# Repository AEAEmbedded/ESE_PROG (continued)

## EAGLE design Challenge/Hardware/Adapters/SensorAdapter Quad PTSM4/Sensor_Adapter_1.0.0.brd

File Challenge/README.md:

# Challenge

This folder contains resources for the Prog6 Challenge project.

## Repositories

- **[PiTest](https://github.com/jakorten/PiTest)** - Raspberry Pi 4 to SensorHub (SAMD21) I2C communication test
  - Python I2C test script for Pi
  - C++ Arduino sketch for SAMD21
  - Pinout documentation

## Contents

- **HAN_Challenge_Prog_6_2025.pdf** - Challenge assignment document (2025 edition; to be updated for 2026-2027)
- **Hardware/** - Hardware design files and schematics

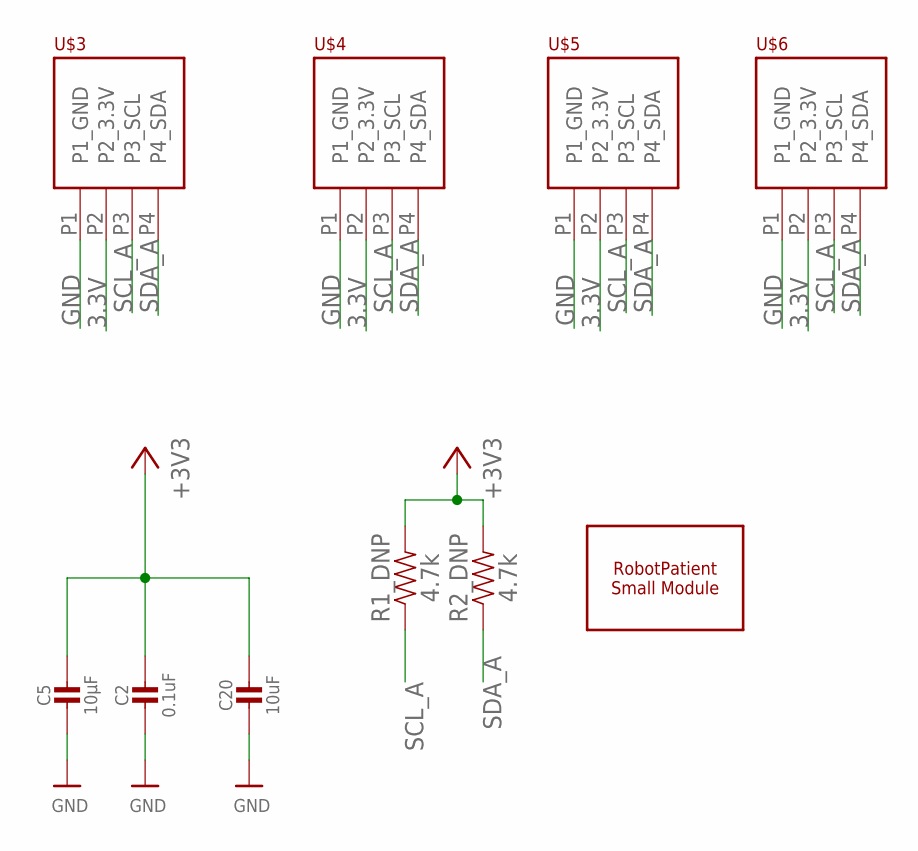
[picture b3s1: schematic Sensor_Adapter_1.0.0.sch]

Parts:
C2: 0.1uF; 0603
C5: 10µF; 0805
C20: 10uF; 0805
R1_DNP, R2_DNP: 4.7k; 0603
U$1: ROBOTPATIENT_SMALL_MODULEBOARD; RP_SMALL_SENSOR_OUTLINE
U$3, U$4, U$5, U$6: PHOENIX_PTSM_M4_THANGLE; PTSM_M4_TH

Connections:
3.3V: C2.1, C5.1, C20.1, R1_DNP.2, R2_DNP.2, U$3.P2 (P2_3.3V), U$4.P2 (P2_3.3V), U$5.P2 (P2_3.3V), U$6.P2 (P2_3.3V)
GND: C2.2, C5.2, C20.2, U$3.P1 (P1_GND), U$4.P1 (P1_GND), U$5.P1 (P1_GND), U$6.P1 (P1_GND)
SCL_A: R1_DNP.1, U$3.P3 (P3_SCL), U$4.P3 (P3_SCL), U$5.P3 (P3_SCL), U$6.P3 (P3_SCL)
SDA_A: R2_DNP.1, U$3.P4 (P4_SDA), U$4.P4 (P4_SDA), U$5.P4 (P4_SDA), U$6.P4 (P4_SDA)

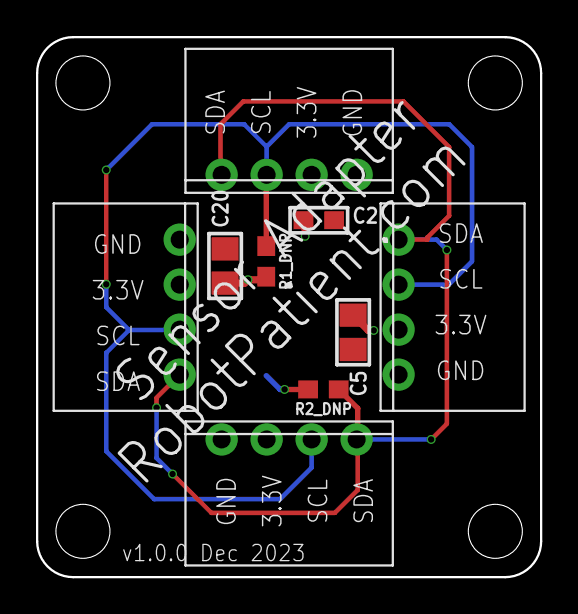
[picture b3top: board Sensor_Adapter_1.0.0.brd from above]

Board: 2 copper layers, 28.0 x 30.0 mm, 10 parts (0 on the bottom side), 4 nets.

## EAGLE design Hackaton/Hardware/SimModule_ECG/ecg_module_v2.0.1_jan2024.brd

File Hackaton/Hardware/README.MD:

# Patient Monitoring System on Raspberry Pi 3

This project involves creating a patient monitoring system using Raspberry Pi 3, which interfaces with various medical sensor modules (ECG, SpO2, NIBP, Temperature) via I2C and other communication protocols. The system features a simple and intuitive user interface for real-time monitoring.

### Table of Contents

- Overview
- Hardware Requirements
- Software Requirements
- Setup Guide
- System Architecture
- Usage
- Future Enhancements
- Overview

## The Patient Monitoring System collects and displays vital signs such as:

- ECG (Electrocardiogram)
- SpO2 (Oxygen Saturation)
- NIBP (Non-Invasive Blood Pressure)
- Temperature

The system is modular and allows integration of additional sensors through standardized adapters and communication protocols.

## Hardware Requirements

Raspberry Pi 3 (or higher) with GPIO-enabled interface

### Sensor Modules:
- ECG: ecg_leaddetection_module
- SpO2: spo2_module
- Temperature: temp_module
- NIBP: Pressure_Module

### Adapters:
- SensorAdapter Quad PTSM4
- SimModule Adapter

### Connections:
- I2C: SDA (GPIO2) and SCL (GPIO3)
- UART or SPI (if required by modules)

Refer to the provided .brd and .sch files for hardware schematics.

  * [hardware](./)
    * [Adapters](./Adapters) - PCB schematics and board files for adapters
    * [SimModule_ECG](./SimModule_ECG) - ECG sensor module files
    * [SimModule_NIBP](./SimModule_NIBP) - Blood pressure (NIBP) module files
    * [SimModule_SpO2](./SimModule_SpO2) - SpO2 (Oxygen saturation) module files
    * [SimModule_Temperature](./SimModule_Temperature) - Temperature module files
  * [README.md](README.md) - Documentation file (this file)

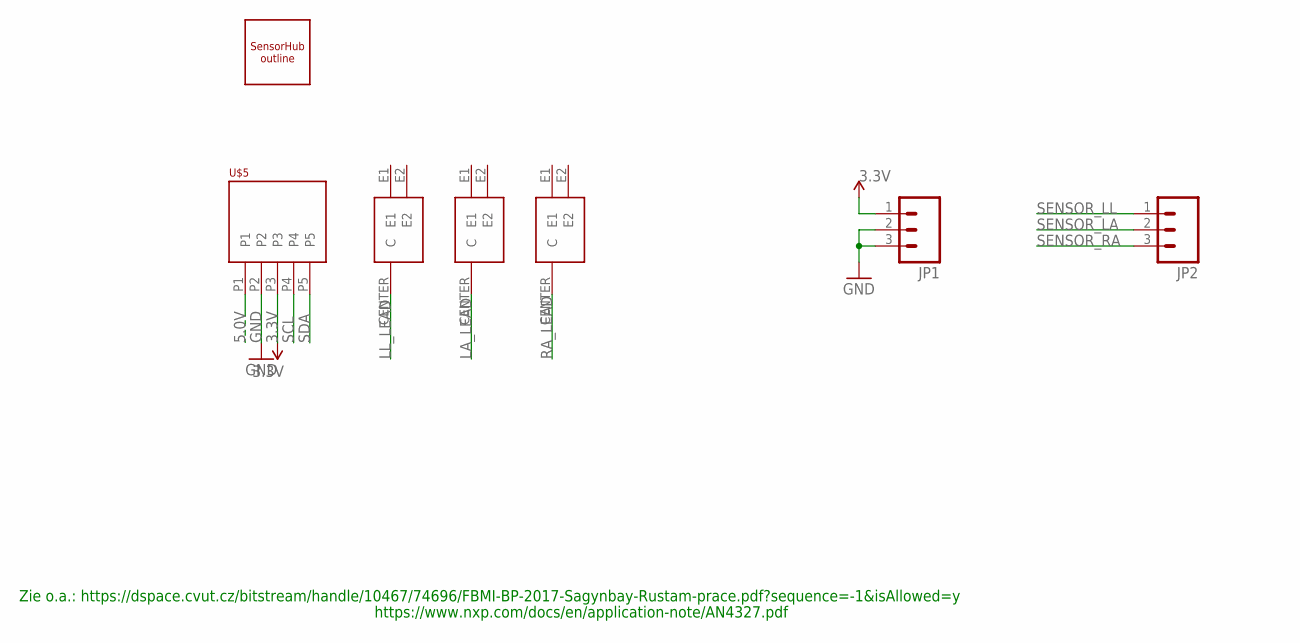
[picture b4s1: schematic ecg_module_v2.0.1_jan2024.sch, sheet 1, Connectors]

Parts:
JP1, JP2: M03PTH; 1X03
U$1, U$3, U$4: DIN_ECG_EEG; EEG_ECG_DIN
U$5: PHOENIX_PTSM_M5_TH_I2C++; PTSM_M5_THRHOLE
U$12: SENSORHUB_PROFILEUSB_LEFT; SENSORHUB_OUTLINE_USB_NOTCH_LEFT

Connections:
3.3V: JP1.1, U$5.P3; also elsewhere on the board
5.0V: U$5.P1; also elsewhere on the board
GND: JP1.2, JP1.3, U$5.P2; also elsewhere on the board
LA_LEAD: U$3.CENTER (C); also elsewhere on the board
LL_LEAD: U$1.CENTER (C); also elsewhere on the board
RA_LEAD: U$4.CENTER (C); also elsewhere on the board
SCL: U$5.P4; also elsewhere on the board
SDA: U$5.P5; also elsewhere on the board
SENSOR_LA: JP2.2; also elsewhere on the board
SENSOR_LL: JP2.1; also elsewhere on the board
SENSOR_RA: JP2.3; also elsewhere on the board

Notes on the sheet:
Zie o.a.: https://dspace.cvut.cz/bitstream/handle/10467/74696/FBMI-BP-2017-Sagynbay-Rustam-prace.pdf?sequence=-1&isAllowed=y
https://www.nxp.com/docs/en/application-note/AN4327.pdf

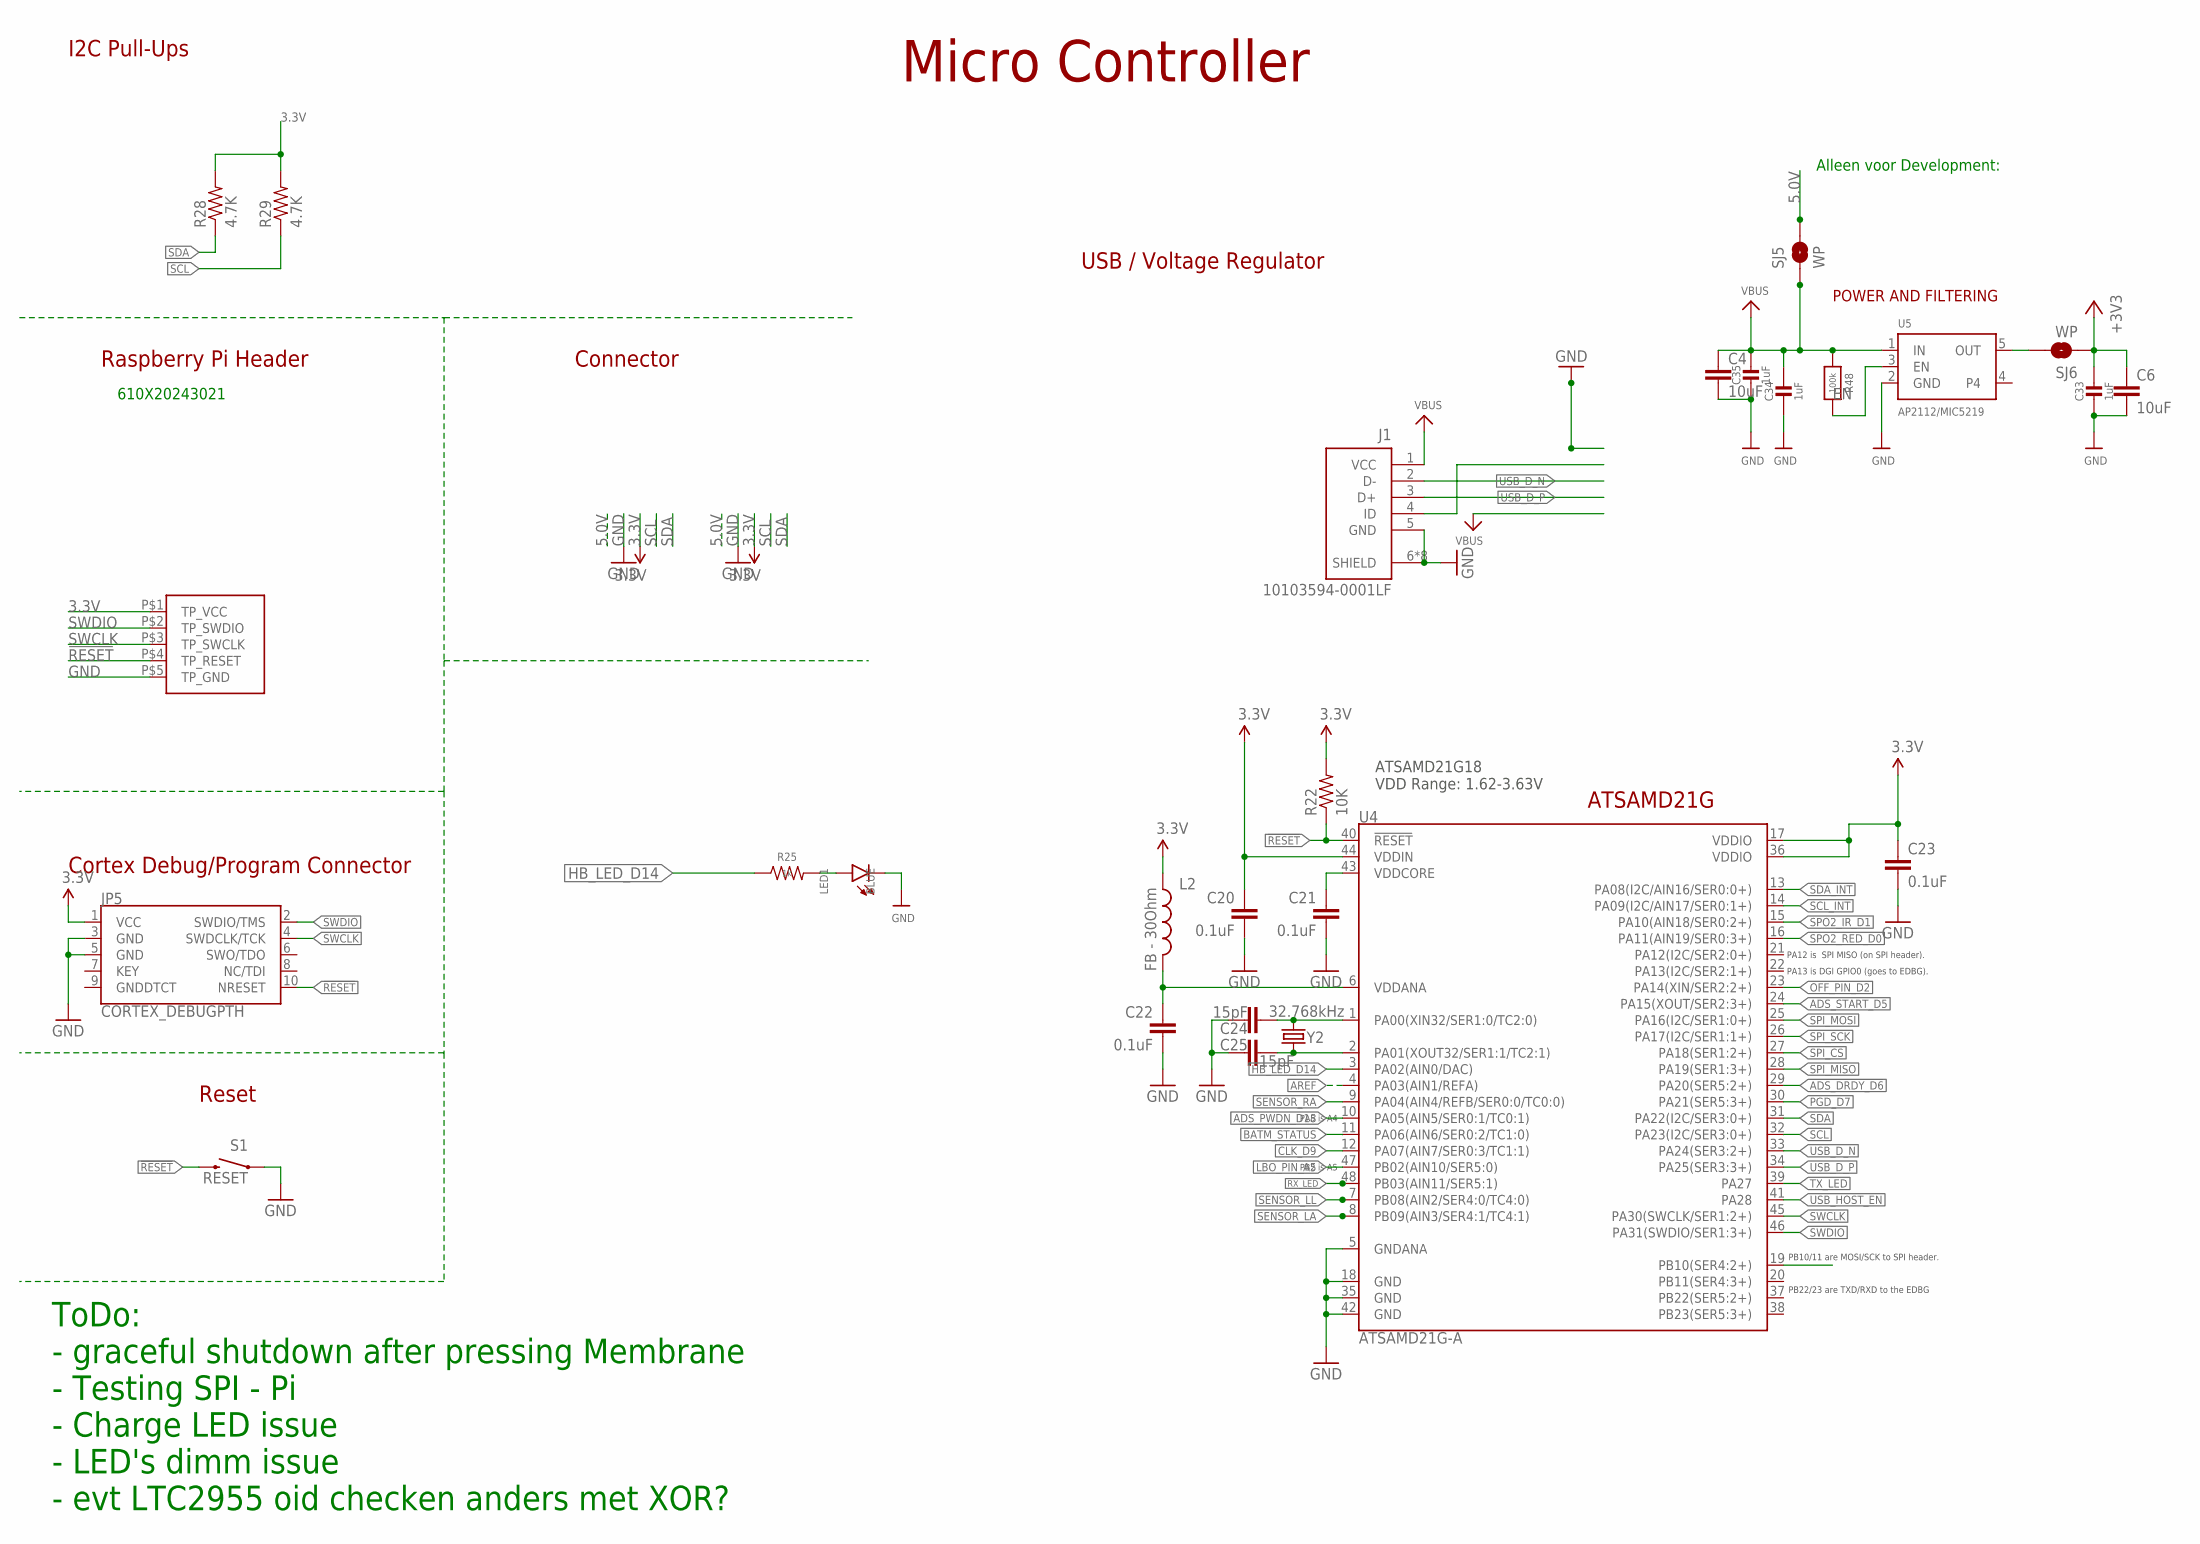
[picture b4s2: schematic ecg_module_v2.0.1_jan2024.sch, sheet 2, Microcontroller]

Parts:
C4, C6: 10uF; 0603
C20, C22, C23: 0.1uF; 0402-CAP
C21: 0.1uF; 0603
C24, C25: 15pF; 0402-CAP
C33, C34, C35: 1uF; 0603-NO
J1: 10103594-0001LF; AMPHENOL_10103594-0001LF
JP5: CORTEX_DEBUGPTH; 2X5-PTH-1.27MM
L2: FB - 30Ohm; 0603
LED1: BLUE; CHIP-LED0603
R22: 10K; 0603-RES
R25: 1k; 0603
R28, R29: 4.7K; 0603-RES
R48: 100k; 0603-NO@1
S1: RESET; TACTILE_SWITCH_SMD_4.6X2.8MM
SJ5, SJ6: WP; SMT-JUMPER_2_NO_NO-SILK
U4: ATSAMD21G-A; TQFP-48
U5: AP2112/MIC5219; SOT23-5
U$9: HUB_TESTPINSHUBS; TEST_PINS
Y2: 32.768kHz; CRYSTAL-SMD-3.2X1.5MM

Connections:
3.3V: C6.1, C20.1, C23.1, C33.1, JP5.1 (VCC), L2.1, R22.2, R28.2, R29.2, SJ6.1, U4.17 (VDDIO), U4.36 (VDDIO), U4.44 (VDDIN), U$9.P$1 (TP_VCC); also elsewhere on the board
5.0V: SJ5.2; also elsewhere on the board
!ADS_DRDY_D6: U4.29 (PA20(SER5:2+)); also elsewhere on the board
!RESET: JP5.10 (NRESET), R22.1, S1.3 (2), S1.4 (2), U4.40 (!RESET!), U$9.P$4 (TP_RESET)
ADS_PWDN_D18: U4.10 (PA05(AIN5/SER0:1/TC0:1)); also elsewhere on the board
ADS_START_D5: U4.24 (PA15(XOUT/SER2:3+)); also elsewhere on the board
AREF: U4.4 (PA03(AIN1/REFA))
BATM_STATUS: U4.11 (PA06(AIN6/SER0:2/TC1:0))
CLK_D9: U4.12 (PA07(AIN7/SER0:3/TC1:1)); also elsewhere on the board
EN: R48.2, U5.3 (EN)
GND: C4.2, C6.2, C20.2, C21.2, C22.2, C23.2, C24.1, C25.2, C33.2, C34.2, C35.2, J1.5 (GND), J1.6 (SHIELD), J1.7 (SHIELD), J1.8 (SHIELD), J1.9 (SHIELD), J1.10 (SHIELD), J1.11 (SHIELD), J1.S1 (SHIELD), J1.S2 (SHIELD), JP5.3 (GND), JP5.5 (GND), LED1.C, S1.1, S1.2 (1), U4.5 (GNDANA), U4.18 (GND), U4.35 (GND), U4.42 (GND), U5.2 (GND), U$9.P$5 (TP_GND); also elsewhere on the board
HB_LED_D14: R25.1, U4.3 (PA02(AIN0/DAC))
LBO_PIN_A5: U4.47 (PB02(AIN10/SER5:0))
unnamed: LED1.A, R25.2
unnamed: C24.2, U4.1 (PA00(XIN32/SER1:0/TC2:0)), Y2.P$2 (2)
unnamed: C25.1, U4.2 (PA01(XOUT32/SER1:1/TC2:1)), Y2.P$1 (1)
OFF_PIN_D2: U4.23 (PA14(XIN/SER2:2+))
OUT: SJ6.2, U5.5 (OUT)
PGD_D7: U4.30 (PA21(SER5:3+))
RX_LED: U4.48 (PB03(AIN11/SER5:1))
SCL: R29.1, U4.32 (PA23(I2C/SER3:0+)); also elsewhere on the board
SCL_INT: U4.14 (PA09(I2C/AIN17/SER0:1+))
SDA: R28.1, U4.31 (PA22(I2C/SER3:0+)); also elsewhere on the board
SDA_INT: U4.13 (PA08(I2C/AIN16/SER0:0+))
SENSOR_LA: U4.8 (PB09(AIN3/SER4:1/TC4:1)); also elsewhere on the board
SENSOR_LL: U4.7 (PB08(AIN2/SER4:0/TC4:0)); also elsewhere on the board
SENSOR_RA: U4.9 (PA04(AIN4/REFB/SER0:0/TC0:0)); also elsewhere on the board
SPI_CS: U4.27 (PA18(SER1:2+)); also elsewhere on the board
SPI_MISO: U4.28 (PA19(SER1:3+)); also elsewhere on the board
SPI_MOSI: U4.25 (PA16(I2C/SER1:0+)); also elsewhere on the board
SPI_SCK: U4.26 (PA17(I2C/SER1:1+)); also elsewhere on the board
SPO2_IR_D1: U4.15 (PA10(AIN18/SER0:2+))
SPO2_RED_D0: U4.16 (PA11(AIN19/SER0:3+))
SWCLK: JP5.4 (SWDCLK/TCK), U4.45 (PA30(SWCLK/SER1:2+)), U$9.P$3 (TP_SWCLK)
SWDIO: JP5.2 (SWDIO/TMS), U4.46 (PA31(SWDIO/SER1:3+)), U$9.P$2 (TP_SWDIO)
TX_LED: U4.39 (PA27)
USB_D_N: J1.2 (D-), U4.33 (PA24(SER3:2+))
USB_D_P: J1.3 (D+), U4.34 (PA25(SER3:3+))
USB_HOST_EN: U4.41 (PA28)
VBUS: C4.1, C34.1, C35.1, J1.1 (VCC), R48.1, SJ5.1, U5.1 (IN)
VDDANA: C22.1, L2.2, U4.6 (VDDANA)
VDDCORE: C21.1, U4.43 (VDDCORE)

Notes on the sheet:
PB22/23 are TXD/RXD to the EDBG
PB10/11 are MOSI/SCK to SPI header.
PA12 is SPI MISO (on SPI header).
PA13 is DGI GPIO0 (goes to EDBG).
PA5 is A4
PB2 is A5
ATSAMD21G
ATSAMD21G18 VDD Range: 1.62-3.63V
Cortex Debug/Program Connector
USB / Voltage Regulator
I2C Pull-Ups
Micro Controller
Raspberry Pi Header
Connector
Reset
ToDo: - graceful shutdown after pressing Membrane - Testing SPI - Pi - Charge LED issue - LED's dimm issue - evt LTC2955 oid checken anders met XOR?
610X20243021
POWER AND FILTERING
Alleen voor Development:

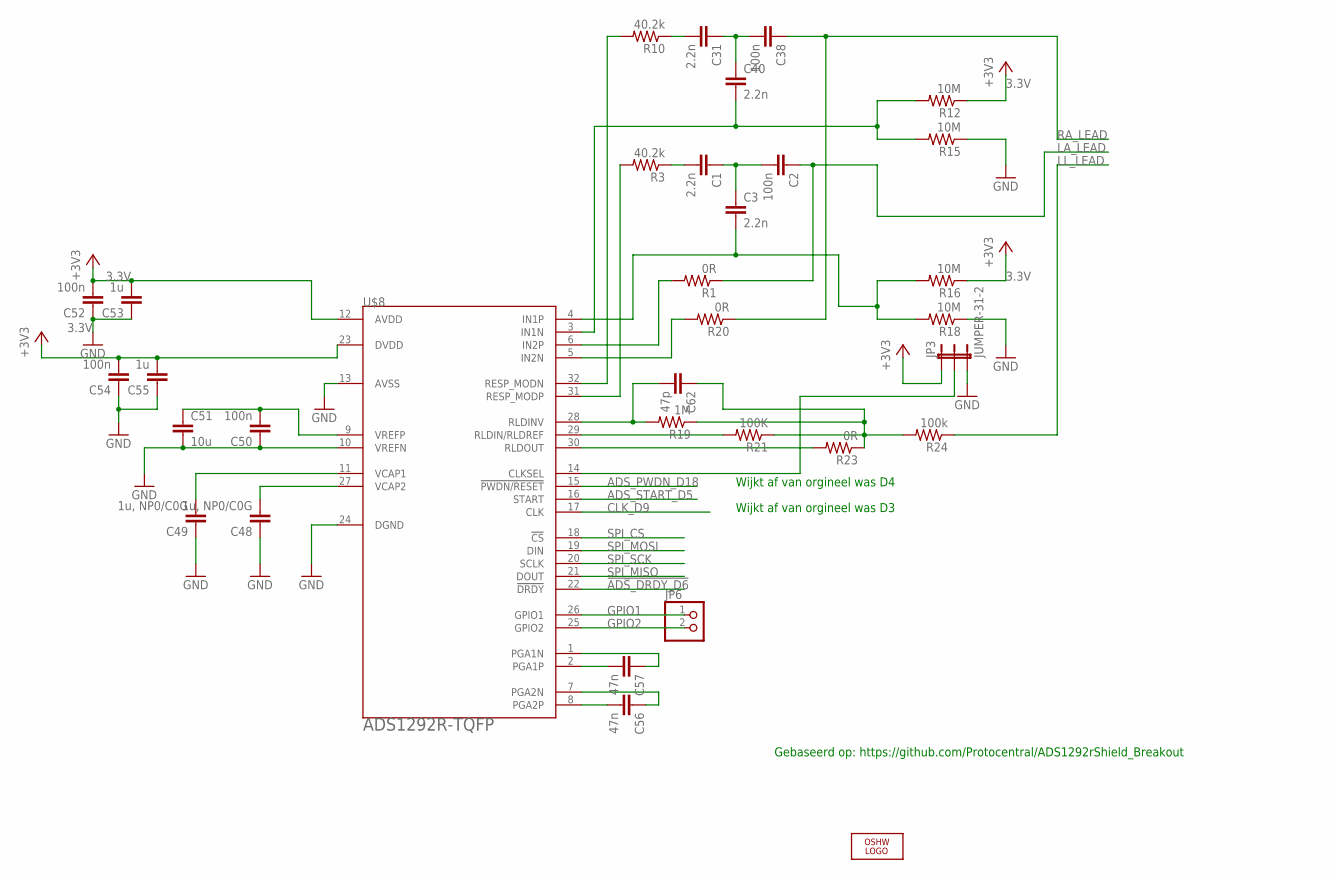
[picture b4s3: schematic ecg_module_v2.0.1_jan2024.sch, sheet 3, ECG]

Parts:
C1, C3, C31, C40: 2.2n; C0402
C2, C38, C50, C52, C54: 100n; C0402
C48, C49: 1u, NP0/C0G; C0402
C51: 10u; C0603
C53, C55: 1u; C0402
C56, C57: 47n; C0402
C62: 47p; C0402
JP3: JUMPER-31-2; SJ_3_PASTE1&2
JP6: PINHD-1X2; 1X02
LOGO1: OSHW_LOGO_FILLX0100-NT; OSHW_FILLX100_NOTEXT
R1, R20, R23: 0R; R0402
R3, R10: 40.2k; R0402
R12, R15, R16, R18: 10M; R0402
R19: 1M; R0402
R21: 100K; R0402
R24: 100k; R0402
U$8: ADS1292R-TQFP; SQFP-S-5X5-32

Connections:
3.3V: C52.2, C53.2, C54.2, C55.2, JP3.1, R12.1, R16.1, U$8.12 (AVDD), U$8.23 (DVDD); also elsewhere on the board
!ADS_DRDY_D6: U$8.22 (!DRDY); also elsewhere on the board
ADS_PWDN_D18: U$8.15 (!PWDN/RESET); also elsewhere on the board
ADS_START_D5: U$8.16 (START); also elsewhere on the board
CLK_D9: U$8.17 (CLK); also elsewhere on the board
GND: C48.1, C49.1, C50.1, C51.2, C52.1, C53.1, C54.1, C55.1, JP3.3, R15.1, R18.1, U$8.10 (VREFN), U$8.13 (AVSS), U$8.24 (DGND); also elsewhere on the board
GPIO1: JP6.1, U$8.26 (GPIO1)
GPIO2: JP6.2, U$8.25 (GPIO2)
LA_LEAD: C2.1, R1.1; also elsewhere on the board
LL_LEAD: R24.1; also elsewhere on the board
unnamed: R3.2, U$8.31 (RESP_MODP)
unnamed: C1.2, R3.1
unnamed: C1.1, C2.2, C3.1
unnamed: R1.2, U$8.6 (IN2P)
unnamed: R20.2, U$8.5 (IN2N)
unnamed: C48.2, U$8.27 (VCAP2)
unnamed: R10.2, U$8.32 (RESP_MODN)
unnamed: C31.2, R10.1
unnamed: C31.1, C38.2, C40.1
unnamed: C40.2, R12.2, R15.2, U$8.3 (IN1N)
unnamed: C3.2, R16.2, R18.2, U$8.4 (IN1P)
unnamed: R21.2, U$8.29 (RLDIN/RLDREF)
unnamed: C62.2, R19.2, U$8.28 (RLDINV)
unnamed: C62.1, R19.1, R21.1, R23.1, R24.2
unnamed: C49.2, U$8.11 (VCAP1)
unnamed: C56.2, U$8.8 (PGA2P)
unnamed: C56.1, U$8.7 (PGA2N)
unnamed: C50.2, C51.1, U$8.9 (VREFP)
unnamed: C57.2, U$8.2 (PGA1P)
unnamed: C57.1, U$8.1 (PGA1N)
unnamed: R23.2, U$8.30 (RLDOUT)
unnamed: JP3.2, U$8.14 (CLKSEL)
RA_LEAD: C38.1, R20.1; also elsewhere on the board
SPI_CS: U$8.18 (!CS); also elsewhere on the board
SPI_MISO: U$8.21 (DOUT); also elsewhere on the board
SPI_MOSI: U$8.19 (DIN); also elsewhere on the board
SPI_SCK: U$8.20 (SCLK); also elsewhere on the board

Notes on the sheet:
Gebaseerd op: https://github.com/Protocentral/ADS1292rShield_Breakout
Wijkt af van orgineel was D3
Wijkt af van orgineel was D4

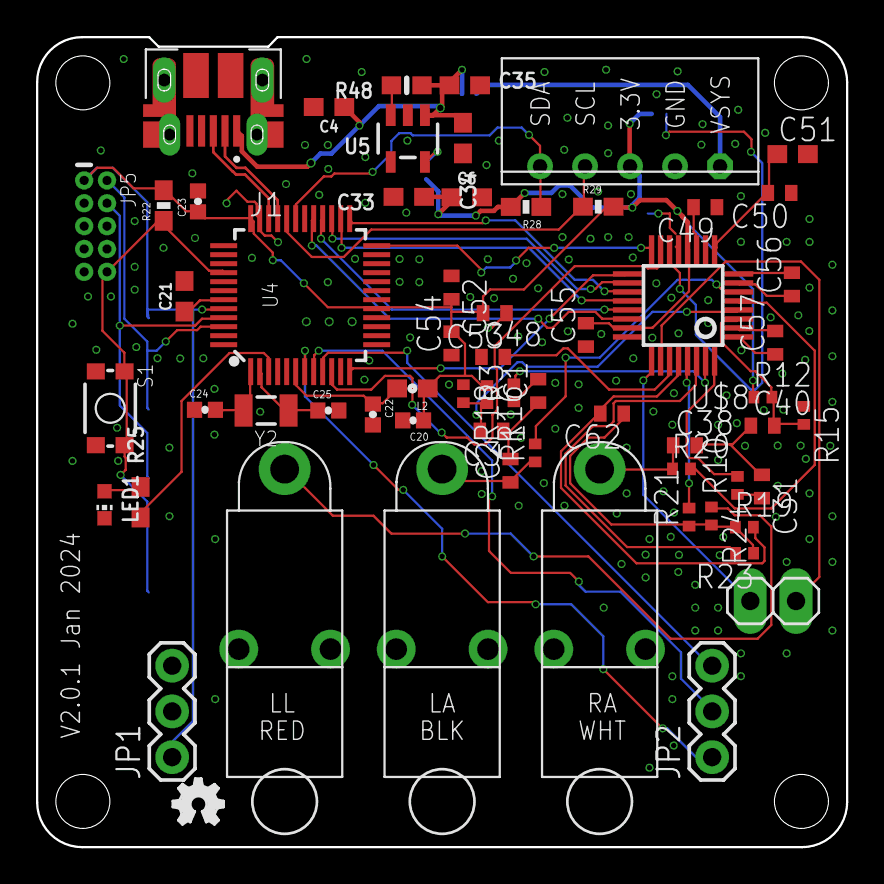
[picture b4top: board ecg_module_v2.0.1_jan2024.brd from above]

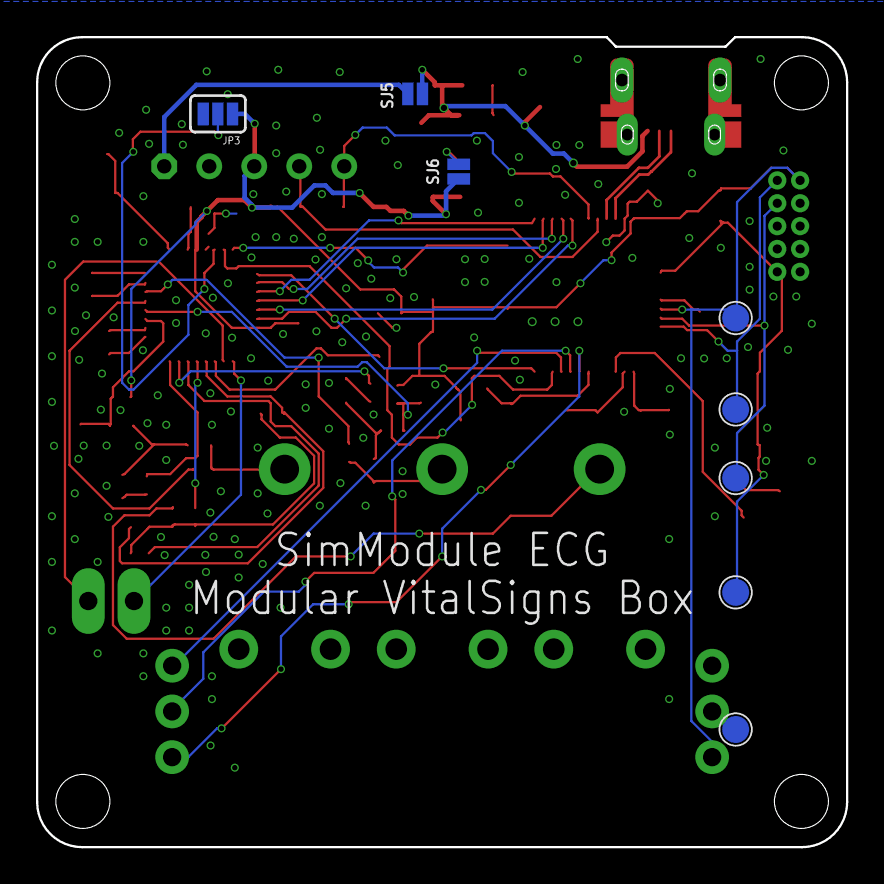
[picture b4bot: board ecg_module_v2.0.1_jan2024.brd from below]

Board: 2 copper layers, 45.0 x 45.0 mm, 67 parts (3 on the bottom side), 57 nets.

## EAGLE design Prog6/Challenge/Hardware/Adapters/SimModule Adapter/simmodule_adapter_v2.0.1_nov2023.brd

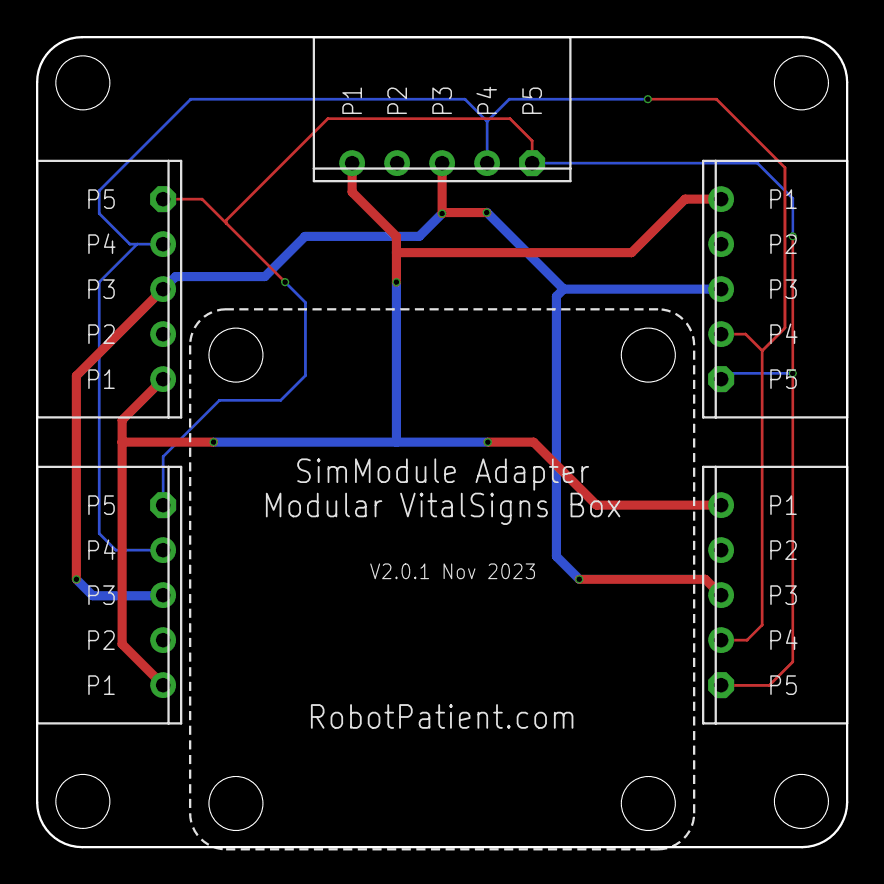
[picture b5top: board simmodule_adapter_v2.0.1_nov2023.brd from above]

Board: 2 copper layers, 45.0 x 45.0 mm, 7 parts (0 on the bottom side), 5 nets.

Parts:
U$1: SENSORHUB_PROFILEBOARD; SENSORHUB_OUTLINE
U$2: ROBOTPATIENT_SMALL_MODULEOUTLINE; ROBOTPATIENT_SMALL
U$3, U$4, U$5, U$6, U$7: PHOENIX_PTSM_M5_NEUTRAL; PTSM_M5_TH_NEUTRAL

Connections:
A: U$3.P1, U$4.P1, U$5.P1, U$6.P1, U$7.P1
B: U$3.P2, U$4.P2, U$5.P2, U$6.P2, U$7.P2
C: U$3.P3, U$4.P3, U$5.P3, U$6.P3, U$7.P3
E: U$3.P5, U$4.P5, U$5.P5, U$6.P5, U$7.P5
GND: U$3.P4, U$4.P4, U$5.P4, U$6.P4, U$7.P4

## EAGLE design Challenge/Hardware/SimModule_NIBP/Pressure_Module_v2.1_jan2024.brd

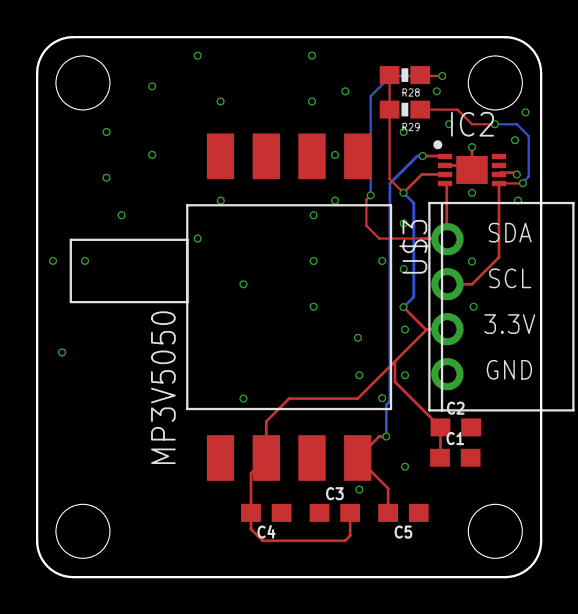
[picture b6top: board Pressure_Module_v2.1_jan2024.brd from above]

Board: 2 copper layers, 28.0 x 30.0 mm, 11 parts (0 on the bottom side), 5 nets.

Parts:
C1: 0.1uF; 0603
C2: 10uF; 0603
C3: 1.0uF; 0603
C4: 10nF; 0603
C5: 470pF; 0603
IC2: MCP3426A0-E_MC; SON50P300X200X100-9N
R28, R29: 4.7K; 0603-RES
U$1: PHOENIX_PTSM_M4_THANGLE; PTSM_M4_TH
U$2: ROBOTPATIENT_SMALL_MODULEBOARD; RP_SMALL_SENSOR_OUTLINE
U$3: MP3V5050; PRESSURE_SENSOR

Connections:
3.3V: C1.1, C2.1, C3.2, C4.2, IC2.3, R28.2, R29.2, U$1.P2, U$3.2
A0_PRESSURE: C5.2, IC2.1, U$3.4
GND: C1.2, C2.2, C3.1, C4.1, C5.1, IC2.2, IC2.6, IC2.8, IC2.9, U$1.P1, U$3.3
SCL: IC2.5, R29.1, U$1.P3
SDA: IC2.4, R28.1, U$1.P4

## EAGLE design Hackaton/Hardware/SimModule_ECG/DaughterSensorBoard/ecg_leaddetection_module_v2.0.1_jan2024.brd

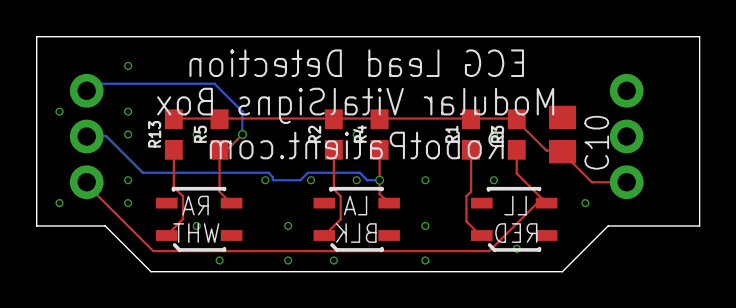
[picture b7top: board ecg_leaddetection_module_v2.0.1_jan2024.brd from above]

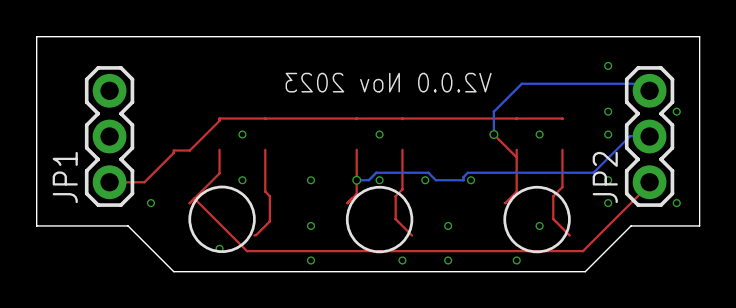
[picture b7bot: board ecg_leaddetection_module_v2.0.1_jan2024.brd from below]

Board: 2 copper layers, 36.8 x 13.1 mm, 12 parts (2 on the bottom side), 8 nets.

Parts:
C10: 10µF; C0805
JP1, JP2: 1X03
R1, R2, R13: 100; 0603
R3, R4, R5: 10k; 0603
U$6, U$7, U$8: QRE1113

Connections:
3.3V: C10.2, JP1.1, R1.2, R2.2, R3.2, R4.2, R5.2, R13.2
GND: C10.1, JP1.2, JP1.3, U$6.2, U$6.4, U$7.2, U$7.4, U$8.2, U$8.4
unnamed: R1.1, U$8.1
unnamed: R2.1, U$7.1
unnamed: R13.1, U$6.1
SENSOR_LA: JP2.2, R4.1, U$7.3
SENSOR_LL: JP2.1, R3.1, U$8.3
SENSOR_RA: JP2.3, R5.1, U$6.3

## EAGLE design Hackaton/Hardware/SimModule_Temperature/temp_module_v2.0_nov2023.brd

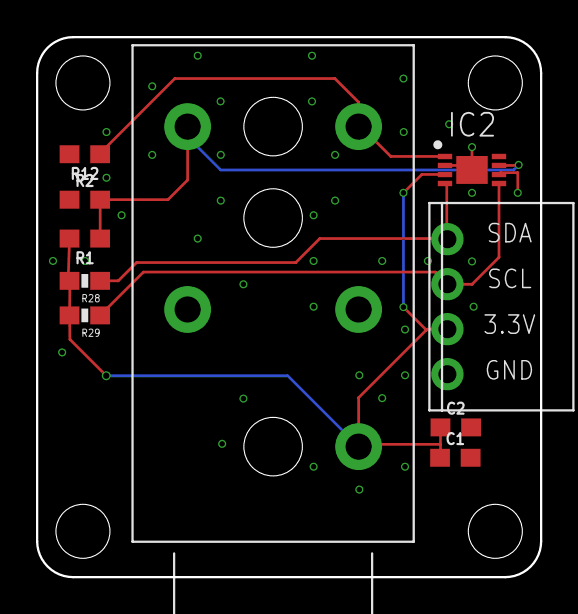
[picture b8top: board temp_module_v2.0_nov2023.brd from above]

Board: 2 copper layers, 28.0 x 30.0 mm, 11 parts (0 on the bottom side), 6 nets.

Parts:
C1: 0.1uF; 0603
C2: 10uF; 0603
IC2: MCP3426A0-E_MC; SON50P300X200X100-9N
R1, R12: 10k; 0603
R2: 1k; 0603
R28, R29: 4.7K; 0603-RES
T_RECT: SN37A1
U$1: PHOENIX_PTSM_M4_THANGLE; PTSM_M4_TH
U$2: ROBOTPATIENT_SMALL_MODULEBOARD; RP_SMALL_SENSOR_OUTLINE

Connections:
3.3V: C1.1, C2.1, IC2.3, R1.2, R28.2, R29.2, T_RECT.S, U$1.P2
GND: C1.2, C2.2, IC2.2, IC2.6, IC2.8, IC2.9, R2.1, R12.2, U$1.P1
PLUG_TEMP: IC2.7, R1.1, R2.2, T_RECT.TB
SCL: IC2.5, R29.1, U$1.P3
SDA: IC2.4, R28.1, U$1.P4
TEMP_PIN: IC2.1, R12.1, T_RECT.T

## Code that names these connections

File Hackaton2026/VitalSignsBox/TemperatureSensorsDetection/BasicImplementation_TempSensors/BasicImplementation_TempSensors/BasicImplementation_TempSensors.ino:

/*
    Johan Korten
    for HAN ESE, WKZ, Capgemini / GET Hackaton Challenge 2025

    V1.0 Jan 2025

    Based on Wire Slave Sender and Receiver by Nicholas Zambetti <http://www.zambetti.com> March 2006

    For your convenience we implemented:
    - Reading both channels of the MCP3426 (CH1+ and CH2+). This detects if a temperature sensor is connected.
    - Very basic implementation just as proof of concept. (ToDo: serious refactoring ;)).

*/

#include <Wire.h>
#include "WireScanner.h"
#include "TwiPinHelper.h"

// I2C System Bus Configuration
#define W1_SCL 39  // PA13
#define W1_SDA 28  // PA12
#define W2_SCL 13  // PA17
#define W2_SDA 11  // PA16

// Pin Setup for I2C Ports
TwiPinPair portSensorsA(W1_SCL, W1_SDA);
TwiPinPair portSensorsB(W2_SCL, W2_SDA);

TwoWire WireSensorA(&sercom1, W1_SDA, W1_SCL);  // Sensor A
TwoWire WireSensorB(&sercom4, W2_SDA, W2_SCL);  // Sensor B

#define LED_HB 14  // Heartbeat LED

// MCP3426A0 Default Address (A0 connected to GND)
#define MCP3426_ADDR 0x68

// Initialize I2C Scanner
WireScanner scannerSensorA(&WireSensorA, "Sensors A");
WireScanner scannerSensorB(&WireSensorB, "Sensors B");

// Function to Read MCP3426 Channel
float readMCP3426Channel(TwoWire* wire, uint8_t channel) {
  uint8_t configByte = 0x10;  // Start single-shot conversion, 16-bit resolution
  configByte |= (channel << 5);  // Set Channel (0: CH1+, 1: CH2+)
  configByte |= 0x00;  // Gain x1
  
  wire->beginTransmission(MCP3426_ADDR);
  wire->write(configByte);
  wire->endTransmission();
  delay(100);  // Wait for conversion (16-bit mode needs ~100ms)

  wire->requestFrom(MCP3426_ADDR, (uint8_t)3);  // 3 bytes: 2 data + 1 config
  if (wire->available() == 3) {
    uint16_t data = (wire->read() << 8) | wire->read();  // Combine two bytes
    wire->read();  // Read the config byte (not used here)

    if (data & 0x8000) {  // Check for negative value
      data = ~data + 1;
      return -((float)data / 32768.0 * 2.048);  // Scale for ±2.048V
    }
    return (float)data / 32768.0 * 2.048;  // Scale for 16-bit ADC
  }
  return NAN;  // Return Not-a-Number if read failed
}

void setup() {
  delay(1500);
  Serial.begin(115200);
  delay(1500);

  // Start I2C ports
  WireSensorA.begin();
  WireSensorB.begin();

  portSensorsA.setPinPeripheralAltStates();
  portSensorsB.setPinPeripheralStates();

  pinMode(LED_HB, OUTPUT);
  digitalWrite(LED_HB, LOW);

  Serial.println("MCP3426 Dual Sensor Reader Ready...");
  delay(1500);
}

void loop() {
  digitalWrite(LED_HB, HIGH);

  // Read CH1+ and CH2+ on Sensor A
  float sensorA_CH1 = readMCP3426Channel(&WireSensorA, 0);  // Channel 1
  float sensorA_CH2 = readMCP3426Channel(&WireSensorA, 1);  // Channel 2

  // Read CH1+ and CH2+ on Sensor B
  float sensorB_CH1 = readMCP3426Channel(&WireSensorB, 0);  // Channel 1
  float sensorB_CH2 = readMCP3426Channel(&WireSensorB, 1);  // Channel 2

  // Print results
  Serial.println("Sensor A:");
  Serial.print("  CH1+ Voltage: "); Serial.println(sensorA_CH1, 4);
  Serial.print("  CH2+ Voltage: "); Serial.println(sensorA_CH2, 4);

  Serial.println("Sensor B:");
  Serial.print("  CH1+ Voltage: "); Serial.println(sensorB_CH1, 4);
  Serial.print("  CH2+ Voltage: "); Serial.println(sensorB_CH2, 4);

  Serial.println("-------------------------------------");

  digitalWrite(LED_HB, LOW);
  delay(1000);  // 1-second delay between reads
}

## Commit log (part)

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2024-09-20 Updated slides lecture 3
2024-09-20 Changed folder name old rubrics
2024-09-20 Lab week 3
2024-09-20 bugfix: fixed phony parameter in scanForDevice in the VL6180XScanner class
2024-09-20 Added Wirescanner Library for Arduino
2024-09-26 Updated presentations
2024-09-26 Added manuals
2024-09-26 Week 4 updates
2024-09-30 Updated demo etc
2024-09-30 Updated lecture 5 keynote
2024-10-17 Updated keynotes
2024-11-14 Added new rubrics Prog 6
2024-11-21 Added hardware schematics and boards (Eagle)
2024-11-22 Improved name giving
2024-11-22 Delete HAN_Hackaton_Prog_6_2025.pdf
    Renamed Hackathon to Challenge to avoid confusion...
2024-11-22 Added link to Patient Monitor
2024-11-28 Added more hardware and PDF version of schematics
2025-09-04 Update for 2025-2026
2025-09-04 Examples week 1
2025-09-04 Added some hints etc
2025-09-05 Added assignment week 2
2025-09-12 Updated lecture keynotes week 2
2025-09-12 Added whitepaper development methods
2025-09-12 Added whitepaper development methods (NL)
2025-09-12 Added whitepaper development methods (EN)
2025-09-12 Added whitepaper development methods link to presentation
2025-11-17 Added Clean Code workshop details
2025-11-18 Added Code Smell scanner
2025-11-20 Refactored python / SOLID
2025-11-20 Keynote of the workshop on Clean Code
2025-11-20 Added keynote
2025-11-23 Workshop CMake
2025-11-23 Enh improved CMake workshop
2025-11-23 Enh Embedded CMake and updated keynotes
2025-11-30 Unit Testing basics
2025-11-30 Case 2
2025-11-30 Finished Unit Testing
2025-11-30 Added Workshop commenting
2025-12-02 Enh Workshop commenting
2025-12-08 Added source files for hackaton
2025-12-10 minor changes
2025-12-18 Added updated rubrics
2026-01-04 Added Design Patterns update
2026-01-27 Additional info hackaton hw
